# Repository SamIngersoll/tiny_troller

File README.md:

# Tiny Troller v0.1

A tiny STM32 based brushed motor controller with magnetic encoder and LIN communication.

C_BAT on voltage regulator is limiting voltage to 6.3 V (maximum voltage I could find for 22uF, 0402 cap).

Driver chip is rated for 4.5V to 36V, 3A. (Not yet tested).

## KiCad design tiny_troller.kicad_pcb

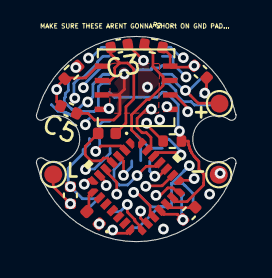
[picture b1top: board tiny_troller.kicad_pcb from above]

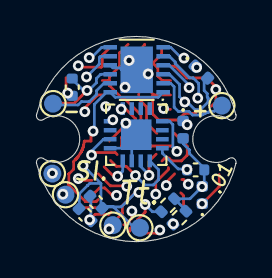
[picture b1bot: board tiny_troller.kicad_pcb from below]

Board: 4 copper layers, 11.1 x 11.4 mm, 32 parts (17 on the bottom side), 30 nets.

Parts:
C1, C6: 10u; C_0402_1005Metric
C2, C3: 100n; C_0402_1005Metric
C4: 220p; C_0402_1005Metric
C5: 22u; C_0402_1005Metric
C7, C8: 1u; C_0402_1005Metric
C9: 0.1u; C_0402_1005Metric
D1: LED (BLUE); LED_0402_1005Metric
D2, D3: CLS10F40,L3F; D_0402_1005Metric
D4: CPDQC24VEU-HF; D_0402_1005Metric
D5: CPDQR24V-HF; D_0402_1005Metric
R1: 1k5; R_0402_1005Metric
R2, R4: 10k; R_0402_1005Metric
R3: 70m; R_0402_1005Metric
R5: 2; R_0402_1005Metric
TP2, TP3, TP4, TP5, TP6, TP7, TP8, TP9, TP10: TestPoint_Small; TestPoint_Pad_D1.0mm
U1: MA702GQ-P; QFN-3x3_MA702_MNP
U3: STM32G071G8U6
U5: MCP2025-330E_MD; MCP2025-330E-MD
U6: MAX14870ETC+T

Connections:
+3V3: C1.2, C2.1, C6.2, C8.2, R2.2, TP4.1, U1.13, U3.3, U5.8
ADC_IN_CURRENT_SENSE: R3.1, U3.6, U6.1, U6.4, U6.12
DRV_DIRECTION: U3.19, U6.6
DRV_ENABLE: U3.2, U6.8
DRV_FAULT: R4.1, U3.1, U6.7
DRV_PWM: U3.28, U6.5
ENC_CS: U1.5, U3.7
ENC_MGH: U1.16, U3.16
ENC_MGL: U1.11, U3.17
ENC_MISO: U1.7, U3.12
ENC_MOSI: U1.4, U3.13
ENC_PWM: U1.9, U3.10
ENC_SCK: U1.12, U3.11
GND: C1.1, C2.2, C3.1, C4.1, C5.1, C6.1, C7.1, C8.1, C9.2, D4.2, D5.2, R1.2, R3.2, R4.2, TP5.1, TP8.1, U1.8, U1.10, U1.17, U3.4, U5.3, U6.9, U6.13
LBUS: C4.2, D5.1, TP6.1, U5.4
LIN_CS: D3.2, U3.18
LIN_RESET: R2.1, U3.14, U5.7
LIN_RX: U3.9, U5.5
LIN_TX: U3.8, U5.6
MOTOR+: TP10.1, U6.2
MOTOR-: TP7.1, U6.11
NRST: C9.1, U3.5
unnamed: C3.2, D3.1, U5.2
unnamed: C5.2, D4.1, R5.1, U5.1
unnamed: D1.1, R1.1
unnamed: D2.1, R5.2
PWR: C7.2, D2.2, TP9.1, U6.3, U6.10
STAT_LED: D1.2, U3.22
SW_SWCLK: TP2.1, U3.21
SW_SWDIO: TP3.1, U3.20

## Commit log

2021-11-11 v0.0: first hardware version. Has known problems, DO NOT ORDER.
2021-11-11 R5 added, circuitry for MCP2025 LIN transceiver and regulator VBB pin should be correct now.
2021-11-13 v01 design first pass done (all components selected for the first time).
2021-11-14 updated BOM for v00 and v01, needs one final look over with attention paid to maximum power and voltage ratings of passives
2021-11-14 included the final v00 BOM
